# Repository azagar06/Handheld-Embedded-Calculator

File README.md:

# Handheld Embedded Calculator

A fully functional handheld calculator developed from concept to physical prototype. This project combines custom C++ firmware, embedded electronics, PCB design, rechargeable power, and a 3D-printed mechanical enclosure in a compact consumer-style device.

## Project Overview

The goal of this project was to design and build a production-oriented handheld electronic device while gaining experience across the complete product-development process.

Rather than stopping at a breadboard prototype, the calculator was progressively redesigned to improve wiring complexity, physical size, reliability, manufacturability, and overall integration.

The project progressed through several hardware iterations:

1. Arduino Uno breadboard prototype
2. ESP32 breadboard redesign
3. Perf-board validation prototype
4. Custom two-layer PCB
5. 3D-printed snap-fit enclosure
6. Final integrated handheld device

## Key Features

- Addition, subtraction, multiplication, and division
- 4x4 matrix-keypad input
- 16x2 I2C LCD output
- Result chaining for consecutive calculations
- Divide-by-zero error handling
- ESP32-based embedded control
- Custom two-layer PCB
- Rechargeable 3.7 V battery system
- TP4056 battery-charging module
- MT3608 voltage step-up module
- 3D-printed snap-fit enclosure

## Tech Stack

- C++
- Arduino framework
- ESP32
- KiCad
- SOLIDWORKS
- PCB design
- Embedded systems
- Electronics prototyping
- 3D printing

## Development Process

### 1. Arduino Breadboard Prototype

The first prototype used an Arduino Uno to validate the calculator's computational logic, keypad input, LCD output, and C++ firmware.

### 2. ESP32 Architecture Migration

After validating the initial design, the system was redesigned around an ESP32 and a four-pin I2C LCD interface.

This reduced wiring complexity and provided a smaller platform for the final handheld device.

### 3. Perf-Board Prototype

An intermediate perf-board version was built before committing to a custom PCB.

This stage validated the electrical architecture, permanent connections, and power delivery in a more durable configuration.

### 4. Custom PCB

A custom two-layer PCB was designed in KiCad around the physical constraints of the handheld enclosure.

The PCB reduced unnecessary board area, simplified the wiring, and improved the reliability and organization of the final assembly.

#### KiCad Schematic

#### KiCad PCB Layout

### 5. Mechanical Enclosure

A compact snap-fit enclosure was designed in SOLIDWORKS to integrate the display, keypad, PCB, battery, charging electronics, and supporting hardware into one handheld device.

The enclosure was manufactured using 3D printing. Printable STL files are included in the repository.

## Final Assembly

The finished system integrates the ESP32, custom firmware, display, keypad, custom PCB, rechargeable power system, and 3D-printed enclosure.

## Firmware

The calculator firmware is located here:

[`handheld_calculator.ino`](Handheld-Embedded-Calculator-Browser-Safe/firmware/handheld_calculator/handheld_calculator.ino)

The firmware uses the following Arduino libraries:

- `Wire`
- `LiquidCrystal_I2C`
- `Keypad`

### ESP32 Pin Assignments

| Function | ESP32 Pins |
| --- | --- |
| I2C SDA | GPIO 21 |
| I2C SCL | GPIO 22 |
| Keypad rows | GPIO 13, 12, 14, and 27 |
| Keypad columns | GPIO 26, 25, 33, and 32 |

The LCD is configured as a 16x2 display using I2C address `0x27`.

## Hardware Design Files

### KiCad

The KiCad project includes:

- `Calc.kicad_pro`
- `Calc.kicad_sch`
- `Calc.kicad_pcb`

[Open the KiCad project folder](Handheld-Embedded-Calculator-Browser-Safe/hardware/kicad/calculator)

### Gerber Files

PCB manufacturing files are provided as:

[`calculator-gerbers.zip`](Handheld-Embedded-Calculator-Browser-Safe/hardware/gerbers/calculator-gerbers.zip)

## Mechanical Design Files

### SOLIDWORKS

The repository contains:

- `Calculator.SLDASM`
- `calcbase.SLDPRT`

[Open the SOLIDWORKS folder](Handheld-Embedded-Calculator-Browser-Safe/mechanical/solidworks)

The larger `calctop.SLDPRT` source file is available in the repository's [Releases](../../releases) section.

### 3D-Printable Files

The following STL files are included:

- `calcbase.STL`
- `calctop.STL`

[Open the STL folder](Handheld-Embedded-Calculator-Browser-Safe/mechanical/stl)

## Engineering Challenges

### Cross-Domain Integration

One of the primary challenges was integrating firmware, custom electronics, PCB design, power electronics, and mechanical components into one functional system.

Electrical and mechanical decisions had to be developed together because changes in one area frequently affected the final assembly.

### Spatial Constraints

The handheld form factor introduced strict space limitations.

Component placement, PCB geometry, wiring, display positioning, battery placement, and enclosure dimensions were optimized to reduce the overall footprint while maintaining functionality.

### Rechargeable Power System

An MT3608 step-up module, 3.7 V rechargeable battery, and TP4056 charger module were integrated to create a rechargeable power system for the calculator.

### Design for Manufacturability

The project was developed beyond a breadboard proof of concept.

Design considerations included:

- Component placement
- Assembly efficiency
- Structural durability
- PCB size
- Low-profile component selection
- Cost-effective component sourcing
- Reduced wiring complexity
- Ease of final assembly

## Repository Structure

```text
Handheld-Embedded-Calculator/
├── README.md
└── Handheld-Embedded-Calculator-Browser-Safe/
    ├── firmware/
    │   └── handheld_calculator/
    │       └── handheld_calculator.ino
    ├── hardware/
    │   ├── kicad/
    │   │   └── calculator/
    │   │       ├── Calc.kicad_pcb
    │   │       ├── Calc.kicad_pro
    │   │       └── Calc.kicad_sch
    │   └── gerbers/
    │       └── calculator-gerbers.zip
    ├── mechanical/
    │   ├── solidworks/
    │   │   ├── Calculator.SLDASM
    │   │   ├── calcbase.SLDPRT
    │   │   └── README.md
    │   └── stl/
    │       ├── calcbase.STL
    │       └── calctop.STL
    ├── images/
    │   ├── arduino-breadboard.png
    │   ├── custom-pcbs.jpg
    │   ├── enclosure.png
    │   ├── esp32-breadboard.png
    │   ├── final-calculator.jpg
    │   ├── internal-electronics.jpg
    │   ├── pcb-layout.png
    │   ├── perf-board.png
    │   └── schematic.png
    └── docs/
        ├── calculator-project-one-page.pdf
        └── calculator-project-portfolio.pdf
```

## Opening the Project Files

- Open `handheld_calculator.ino` using the Arduino IDE.
- Install the `LiquidCrystal_I2C` and `Keypad` libraries if needed.
- Open `Calc.kicad_pro` in KiCad to view the schematic and PCB layout.
- Use `calculator-gerbers.zip` when viewing or ordering the custom PCB.
- Open the `.SLDASM` and `.SLDPRT` files using SOLIDWORKS.
- Download `calctop.SLDPRT` from the Releases section before opening the complete SOLIDWORKS assembly.
- Open the STL files in a compatible 3D-printing slicer.

## Documentation

Printable project summaries are available in the [`docs`](Handheld-Embedded-Calculator-Browser-Safe/docs) folder.

## Author

Adriano Zagar

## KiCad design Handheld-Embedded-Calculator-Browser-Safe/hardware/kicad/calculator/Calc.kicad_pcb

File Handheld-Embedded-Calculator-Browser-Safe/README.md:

# Handheld Embedded Calculator

A fully functional handheld calculator developed from concept to physical prototype. The project combines custom C++ firmware, embedded electronics, PCB design, rechargeable power, and a 3D-printed mechanical enclosure in a compact consumer-style device.

## Project Overview

The goal of this project was to design and build a production-oriented handheld electronic device while gaining experience across the complete product-development process.

The calculator progressed through several hardware iterations: an Arduino Uno breadboard prototype, an ESP32 breadboard redesign, a perf-board validation build, a custom two-layer PCB, and a 3D-printed snap-fit enclosure.

### Key Features

- Addition, subtraction, multiplication, and division
- 4x4 matrix-keypad input
- 16x2 I2C LCD output
- Result chaining for consecutive calculations
- Divide-by-zero error handling
- ESP32-based embedded control
- Rechargeable 3.7 V power system using a TP4056 charger and MT3608 step-up module
- Custom two-layer PCB
- 3D-printed snap-fit enclosure

### Tech Stack

- C++ and Arduino framework
- ESP32
- KiCad
- SOLIDWORKS
- PCB design and manufacturing files
- Embedded systems
- 3D printing

## Development Process

### 1. Arduino Breadboard Prototype

The first prototype used an Arduino Uno to validate the calculator's computational logic, keypad input, LCD output, and firmware.

### 2. ESP32 Architecture Migration

The system was redesigned around an ESP32 and a four-pin I2C LCD interface. This reduced wiring complexity and provided a smaller platform for the handheld design.

### 3. Perf-Board Prototype

An intermediate perf-board version was built before committing to a custom PCB. This stage validated the electrical architecture, permanent connections, and power delivery.

### 4. Custom PCB

A custom two-layer PCB was designed in KiCad around the physical constraints of the enclosure. The design reduced unnecessary board area and simplified final assembly.

#### KiCad Schematic

#### KiCad PCB Layout

### 5. Mechanical Enclosure

A compact snap-fit enclosure was designed in SOLIDWORKS to integrate the display, keypad, PCB, rechargeable power electronics, and supporting hardware. Printable STL files are included in this repository.

The `calctop.SLDPRT` source file is distributed as a GitHub Release asset because GitHub's browser uploader rejected it from the main repository. The printable `calctop.STL` remains available directly in the repository.

## Final Assembly

The finished system integrates the ESP32, custom firmware, display, keypad, custom PCB, rechargeable power system, and 3D-printed enclosure.

## Firmware

The Arduino sketch is located at [`firmware/handheld_calculator/handheld_calculator.ino`](firmware/handheld_calculator/handheld_calculator.ino).

It uses these Arduino libraries:

- `Wire`
- `LiquidCrystal_I2C`
- `Keypad`

Current ESP32 pin assignments:

| Function | Pins |
| --- | --- |
| I2C SDA / SCL | GPIO 21 / GPIO 22 |
| Keypad rows | GPIO 13, 12, 14, 27 |
| Keypad columns | GPIO 26, 25, 33, 32 |

The LCD is configured as a 16x2 display at I2C address `0x27`.

## Engineering Challenges

### Cross-Domain Integration

Firmware, electronics, PCB design, power electronics, and mechanical components had to operate as one system. Electrical and mechanical decisions were developed together because changes in either area affected the final assembly.

### Spatial Constraints

The handheld form factor imposed strict space limitations. Component placement, PCB geometry, wiring, display positioning, and enclosure dimensions were optimized to reduce the overall footprint while maintaining functionality.

### Rechargeable Power System

An MT3608 step-up module, 3.7 V rechargeable battery, and TP4056 charger module were integrated to provide a rechargeable power solution for the calculator.

### Design for Manufacturability

The project was developed beyond a breadboard proof of concept. Design considerations included component placement, assembly efficiency, structural durability, PCB size, low-profile component selection, cost-effective sourcing, and reduced wiring complexity.

## Repository Structure

```text
Handheld-Embedded-Calculator/
├── README.md
├── firmware/
│   └── handheld_calculator/
│       └── handheld_calculator.ino
├── hardware/
│   ├── kicad/
│   │   └── calculator/
│   │       ├── Calc.kicad_pcb
│   │       ├── Calc.kicad_pro
│   │       └── Calc.kicad_sch
│   └── gerbers/
│       └── calculator-gerbers.zip
├── mechanical/
│   ├── solidworks/
│   │   ├── Calculator.SLDASM
│   │   ├── calcbase.SLDPRT
│   │   └── README.md
│   └── stl/
│       ├── calcbase.STL
│       └── calctop.STL
├── images/
│   └── Project photos and design images
└── docs/
    └── Project portfolio PDFs
```

## Opening the Project Files

- Open the firmware sketch with the Arduino IDE and install the `LiquidCrystal_I2C` and `Keypad` libraries if needed.
- Open `Calc.kicad_pro` in KiCad to view the schematic and PCB layout.
- Use the Gerber ZIP when viewing or ordering the PCB from a board manufacturer.
- Open the `.SLDASM` and `.SLDPRT` files in SOLIDWORKS. Download `calctop.SLDPRT` from the repository's Releases section before opening the complete assembly.
- The STL files can be opened directly in most 3D-printing slicers.

## Documentation

Printable one-page project summaries are available in the [`docs`](docs) folder.

## Author

Adriano Zagar

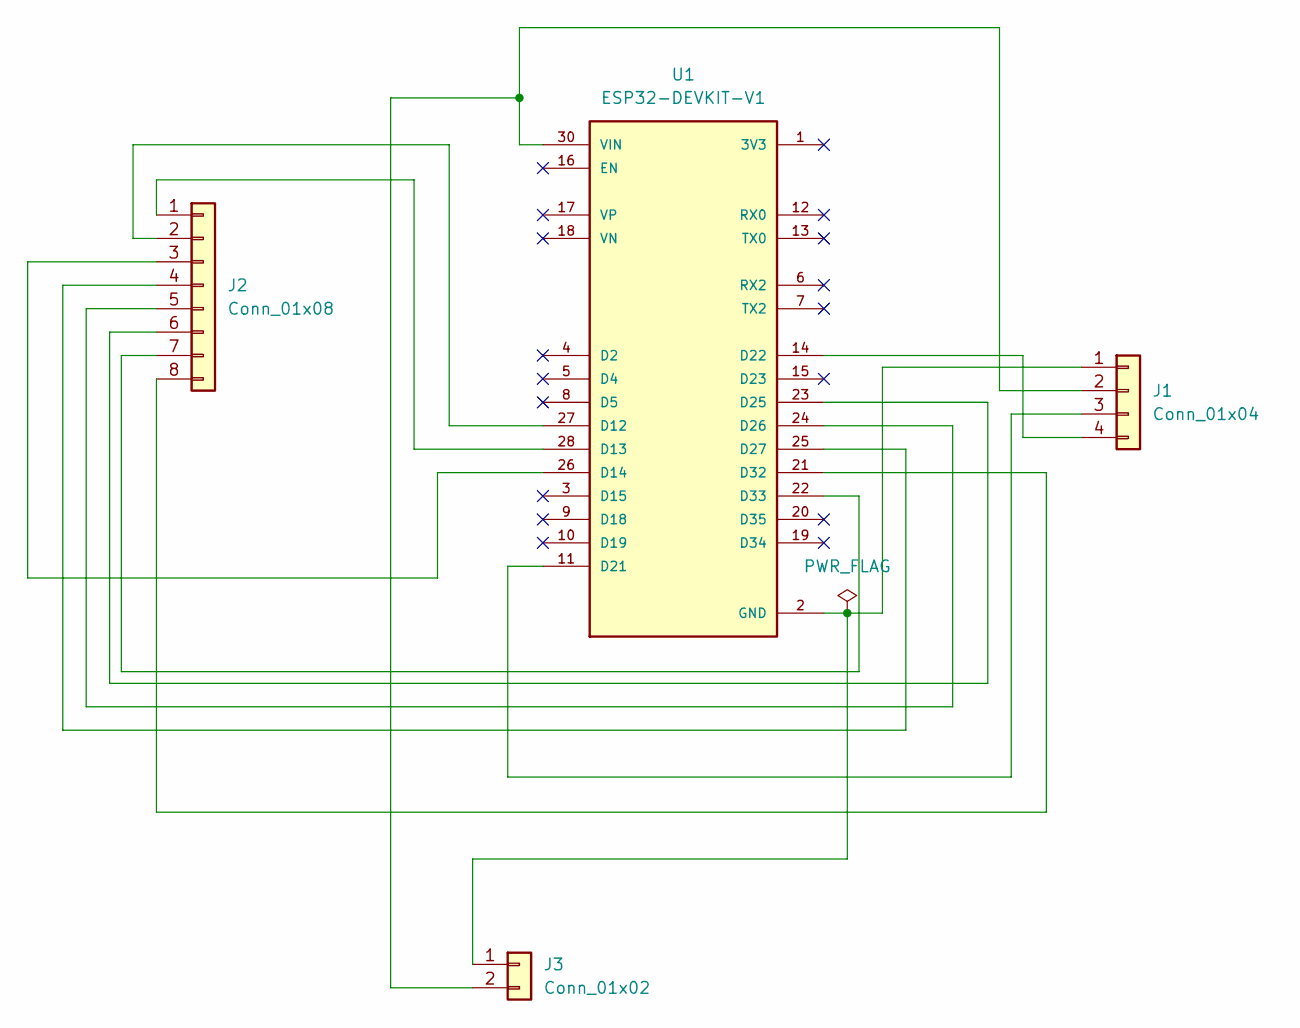
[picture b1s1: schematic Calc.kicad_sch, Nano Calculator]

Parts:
J1: Conn_01x04; PinHeader_1x04_P2.54mm_Vertical
J2: Conn_01x08; PinHeader_1x08_P2.54mm_Vertical
J3: Conn_01x02; PinHeader_1x02_P2.54mm_Vertical
U1: ESP32-DEVKIT-V1; MODULE_ESP32_DEVKIT_V1; PARTREV N/A

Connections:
GND: J1.1, J3.1, U1.2 (GND), U1.29 (GND)
unnamed: J1.2, J3.2, U1.30 (VIN)
unnamed: J1.3, U1.11 (D21)
unnamed: J1.4, U1.14 (D22)
unnamed: J2.1, U1.28 (D13)
unnamed: J2.2, U1.27 (D12)
unnamed: J2.3, U1.26 (D14)
unnamed: J2.4, U1.25 (D27)
unnamed: J2.5, U1.24 (D26)
unnamed: J2.6, U1.23 (D25)
unnamed: J2.7, U1.22 (D33)
unnamed: J2.8, U1.21 (D32)

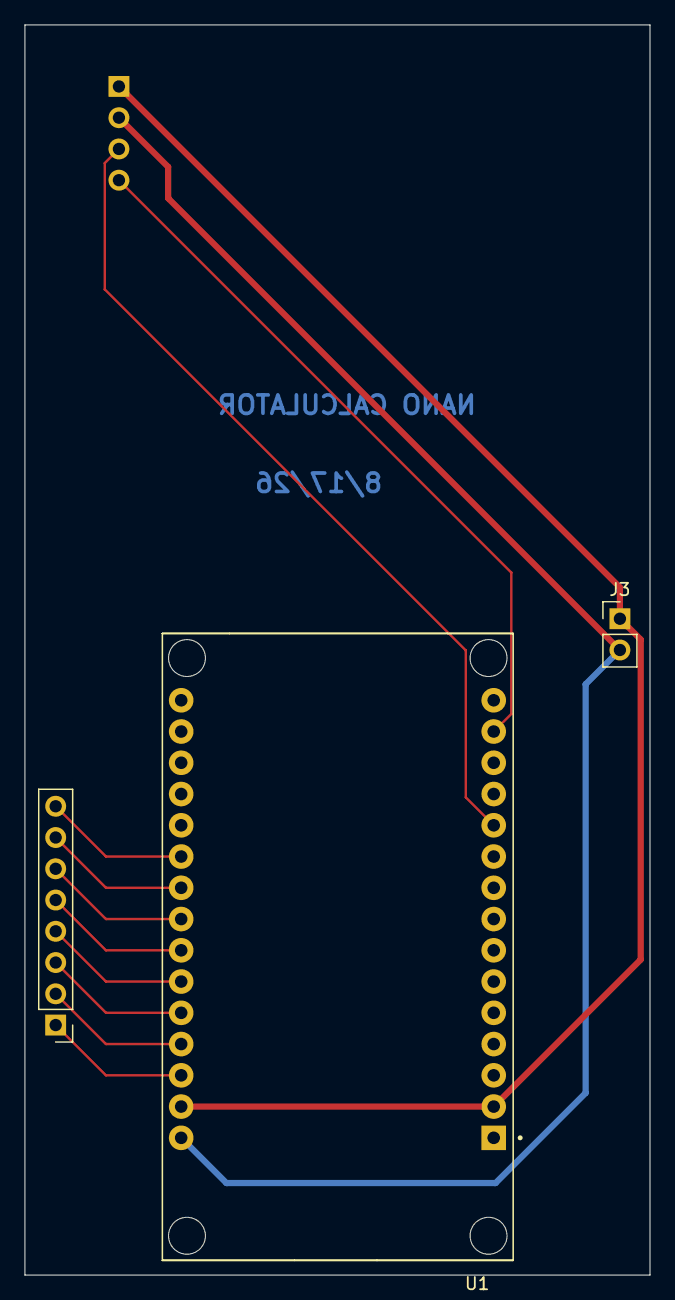
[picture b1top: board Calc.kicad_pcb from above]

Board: 2 copper layers, 50.8 x 101.6 mm, 4 parts (1 on the bottom side), 12 nets.
